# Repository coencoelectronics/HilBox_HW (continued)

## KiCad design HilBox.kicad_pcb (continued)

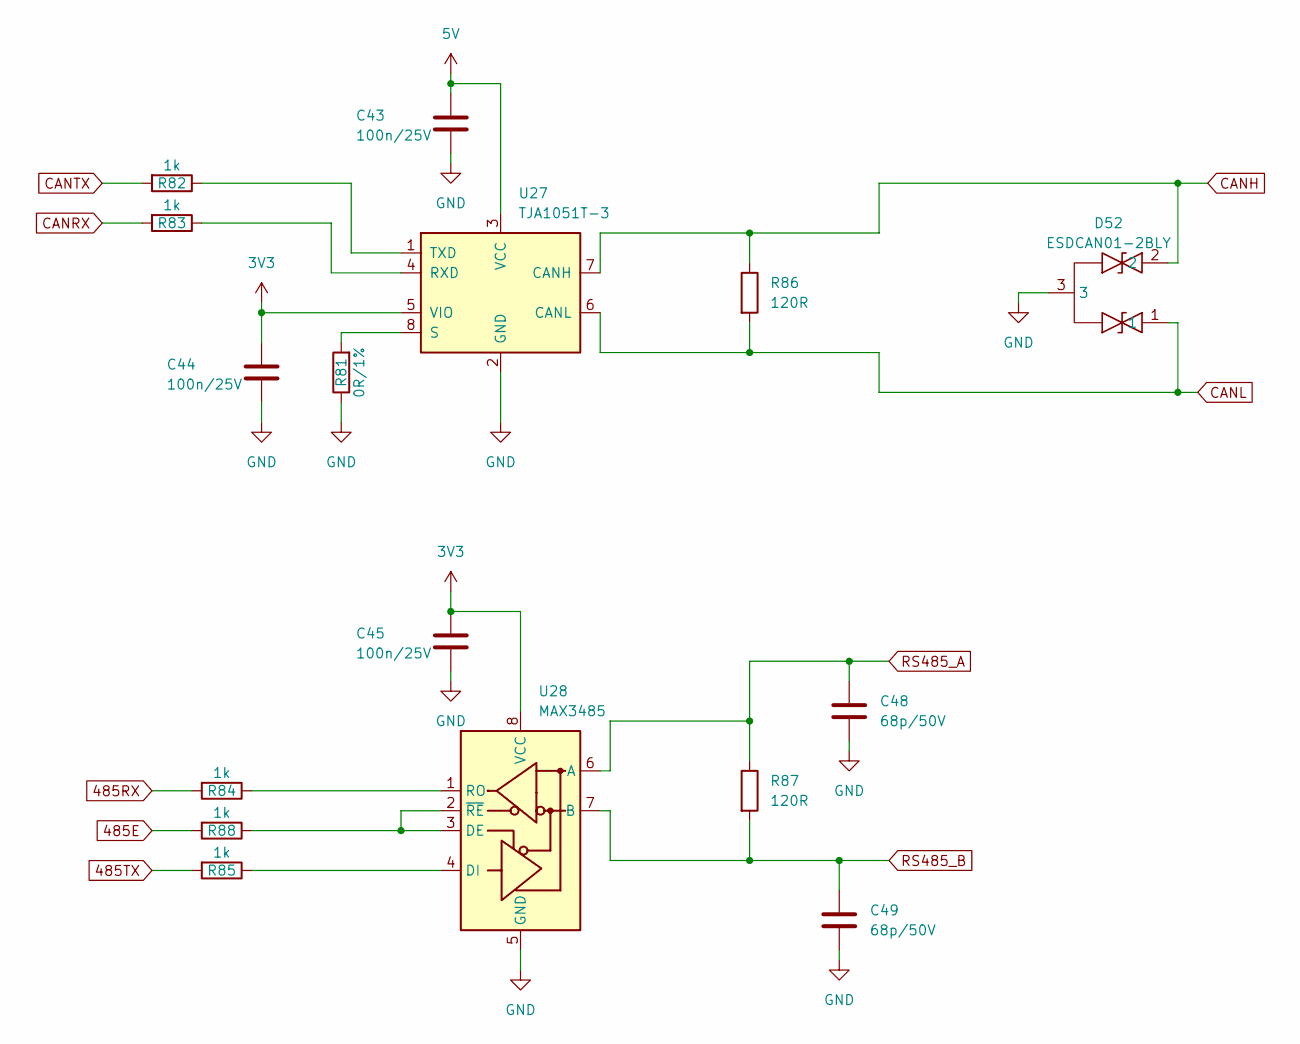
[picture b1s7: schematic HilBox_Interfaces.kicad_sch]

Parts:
C43, C44, C45: 100n/25V; C_0402_1005Metric; JLC_PN C77014
C48, C49: 68p/50V; C_0402_1005Metric; JLC_PN C77014
D52: ESDCAN01-2BLY; SOT-23-3
R81: 0R/1%; R_0603_1608Metric; JLC_PN C21189
R82, R83: 1k; R_1206_3216Metric; JLC_PN C1469
R84, R85, R88: 1k; R_0603_1608Metric; JLC_PN C23162
R86, R87: 120R; R_1210_3225Metric; JLC_PN C137105
U27: TJA1051T-3; SOIC-8_3.9x4.9mm_P1.27mm; JLC_PN C5342108
U28: MAX3485; SOIC-8_3.9x4.9mm_P1.27mm; JLC_PN C558792

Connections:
3V3: C44.1, C45.1, U27.5 (VIO), U28.8 (VCC); also elsewhere on the board
5V: C43.1, U27.3 (VCC); also elsewhere on the board
485E: R88.2; also elsewhere on the board
485RX: R84.2; also elsewhere on the board
485TX: R85.2; also elsewhere on the board
CANH: D52.2, R86.1, U27.7 (CANH); also elsewhere on the board
CANL: D52.1, R86.2, U27.6 (CANL); also elsewhere on the board
CANRX: R83.2; also elsewhere on the board
CANTX: R82.2; also elsewhere on the board
GND: C43.2, C44.2, C45.2, C48.2, C49.2, D52.3, R81.1, U27.2 (GND), U28.5 (GND); also elsewhere on the board
unnamed: R83.1, U27.4 (RXD)
unnamed: R81.2, U27.8 (S)
unnamed: R82.1, U27.1 (TXD)
unnamed: R88.1, U28.2 (~RE), U28.3 (DE)
unnamed: R85.1, U28.4 (DI)
unnamed: R84.1, U28.1 (RO)
RS485_A: C48.1, R87.1, U28.6 (A); also elsewhere on the board
RS485_B: C49.1, R87.2, U28.7 (B); also elsewhere on the board

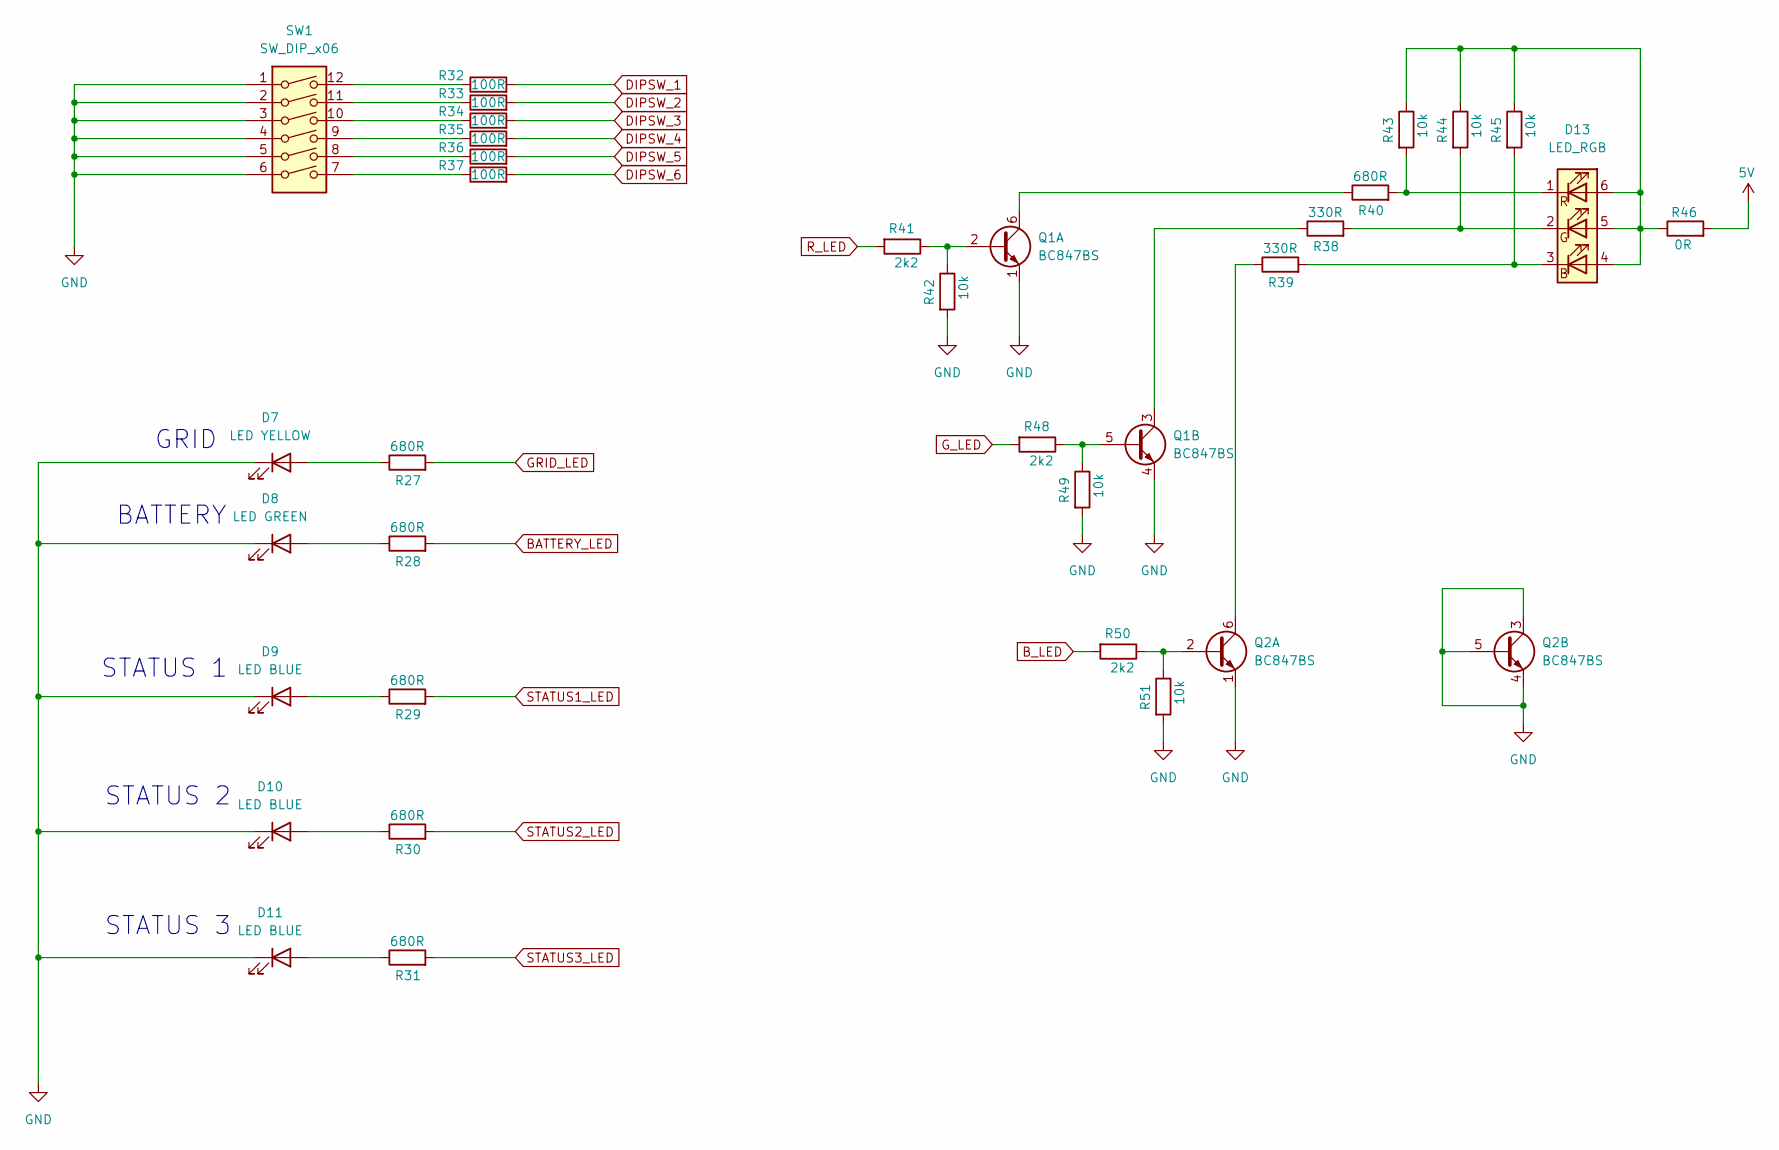
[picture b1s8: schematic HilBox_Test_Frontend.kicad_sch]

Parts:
D7: LED YELLOW; LED_0603_1608Metric; JLC_PN C2290
D8: LED GREEN; LED_0603_1608Metric; JLC_PN C84267
D9, D10, D11: LED BLUE; LED_0603_1608Metric; JLC_PN C2288
D13: LED_RGB; LED_RGB_5050-6; JLC_PN C784540
Q1, Q2: BC847BS; SOT-363_SC-70-6; JLC_PN C82368
R27, R28, R29, R30, R31: 680R; R_0603_1608Metric; JLC_PN C25177
R32, R33, R34, R35, R36, R37: 100R; R_0603_1608Metric; JLC_PN C25138
R38, R39: 330R; R_1206_3216Metric; JLC_PN C25374
R40: 680R; R_1206_3216Metric; JLC_PN C17975
R41, R48, R50: 2k2; R_0603_1608Metric; JLC_PN C4190
R42, R43, R44, R45, R49, R51: 10k; R_0603_1608Metric; JLC_PN C25804
R46: 0R; R_0603_1608Metric; JLC_PN C17168
SW1: SW_DIP_x06; SW_DIP_SPSTx06_Slide_6.7x16.8mm_W8.61mm_P2.54mm_LowProfile; JLC_PN C3293169

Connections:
5V: R46.2; also elsewhere on the board
BATTERY_LED: R28.2; also elsewhere on the board
B_LED: R50.2; also elsewhere on the board
DIPSW_1: R32.2; also elsewhere on the board
DIPSW_2: R33.2; also elsewhere on the board
DIPSW_3: R34.2; also elsewhere on the board
DIPSW_4: R35.2; also elsewhere on the board
DIPSW_5: R36.2; also elsewhere on the board
DIPSW_6: R37.2; also elsewhere on the board
GND: D7.1 (K), D8.1 (K), D9.1 (K), D10.1 (K), D11.1 (K), Q1.1 (E1), Q1.4 (E2), Q2.1 (E1), Q2.3 (C2), Q2.4 (E2), Q2.5 (B2), R42.2, R49.2, R51.2, SW1.1, SW1.2, SW1.3, SW1.4, SW1.5, SW1.6; also elsewhere on the board
GRID_LED: R27.2; also elsewhere on the board
G_LED: R48.2; also elsewhere on the board
unnamed: D7.2 (A), R27.1
unnamed: D8.2 (A), R28.1
unnamed: D9.2 (A), R29.1
unnamed: D10.2 (A), R30.1
unnamed: D11.2 (A), R31.1
unnamed: D13.4 (BA), D13.5 (GA), D13.6 (RA), R43.1, R44.1, R45.1, R46.1
unnamed: D13.3 (BK), R39.2, R45.2
unnamed: D13.2 (GK), R38.2, R44.2
unnamed: D13.1 (RK), R40.2, R43.2
unnamed: Q1.2 (B1), R41.1, R42.1
unnamed: Q1.6 (C1), R40.1
unnamed: Q1.5 (B2), R48.1, R49.1
unnamed: Q1.3 (C2), R38.1
unnamed: Q2.2 (B1), R50.1, R51.1
unnamed: Q2.6 (C1), R39.1
unnamed: R32.1, SW1.12
unnamed: R33.1, SW1.11
unnamed: R34.1, SW1.10
unnamed: R35.1, SW1.9
unnamed: R36.1, SW1.8
unnamed: R37.1, SW1.7
R_LED: R41.2; also elsewhere on the board
STATUS1_LED: R29.2; also elsewhere on the board
STATUS2_LED: R30.2; also elsewhere on the board
STATUS3_LED: R31.2; also elsewhere on the board

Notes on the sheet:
GRID
STATUS 2
STATUS 3
STATUS 1
BATTERY

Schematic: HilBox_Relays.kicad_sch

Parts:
D3, D12, D14, D15: RED; LED_0603_1608Metric; JLC_PN C72038
D4, D16, D19, D21: BAT46W; D_SOD-123; JLC_PN C83152
K1, K2, K3, K4: G6K-2F-Y-24V; RELAY_G6K-2F_DC5; JLC_PN C5278023
Q3, Q8, Q9, Q10: BC847BS; SOT-363_SC-70-6; JLC_PN C82368
R8, R165, R175, R178: 2k2; R_0603_1608Metric; JLC_PN C4190
R9, R11, R65, R67, R70, R164, R176, R177: 10k; R_0603_1608Metric; JLC_PN C25804
R10, R66, R68, R71: 100k; R_0603_1608Metric; JLC_PN C15458
R12, R64, R69, R72: 22k; R_0603_1608Metric; JLC_PN C23344

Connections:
GND: Q3.1 (E1), Q3.4 (E2), Q8.1 (E1), Q8.4 (E2), Q9.1 (E1), Q9.4 (E2), Q10.1 (E1), Q10.4 (E2), R10.2, R11.2, R66.2, R68.2, R71.2, R164.2, R176.2, R177.2; also elsewhere on the board
INAIL_IN: R67.2, R175.2; also elsewhere on the board
unnamed: D3.2 (A), R64.2
unnamed: D3.1 (K), Q9.3 (C2)
unnamed: D4.2 (A), K4.8, Q3.6 (C1)
unnamed: D12.2 (A), R69.2
unnamed: D12.1 (K), Q8.3 (C2)
unnamed: D14.2 (A), R72.2
unnamed: D14.1 (K), Q10.3 (C2)
unnamed: D15.2 (A), R12.2
unnamed: D15.1 (K), Q3.3 (C2)
unnamed: D16.2 (A), K1.8, Q9.6 (C1)
unnamed: D19.2 (A), K2.8, Q8.6 (C1)
unnamed: D21.2 (A), K3.8, Q10.6 (C1)
unnamed: Q3.2 (B1), R8.1, R11.1
unnamed: Q3.5 (B2), R9.1, R10.1
unnamed: Q8.2 (B1), R175.1, R176.1
unnamed: Q8.5 (B2), R67.1, R68.1
unnamed: Q9.2 (B1), R164.1, R165.1
unnamed: Q9.5 (B2), R65.1, R66.1
unnamed: Q10.2 (B1), R177.1, R178.1
unnamed: Q10.5 (B2), R70.1, R71.1
PMING_IN: R70.2, R178.2; also elsewhere on the board
RLY1_A: K1.3; also elsewhere on the board
RLY1_B: K1.4; also elsewhere on the board
RLY2_A: K2.3; also elsewhere on the board
RLY2_B: K2.4; also elsewhere on the board
RLY3_A: K3.3; also elsewhere on the board
RLY3_B: K3.4; also elsewhere on the board
RLY4_A: K4.3; also elsewhere on the board
RLY4_B: K4.4; also elsewhere on the board
RT_IN: R8.2, R9.2; also elsewhere on the board
TL_TF_IN: R65.2, R165.2; also elsewhere on the board
Vin: D4.1 (K), D16.1 (K), D19.1 (K), D21.1 (K), K1.1, K2.1, K3.1, K4.1, R12.1, R64.1, R69.1, R72.1; also elsewhere on the board

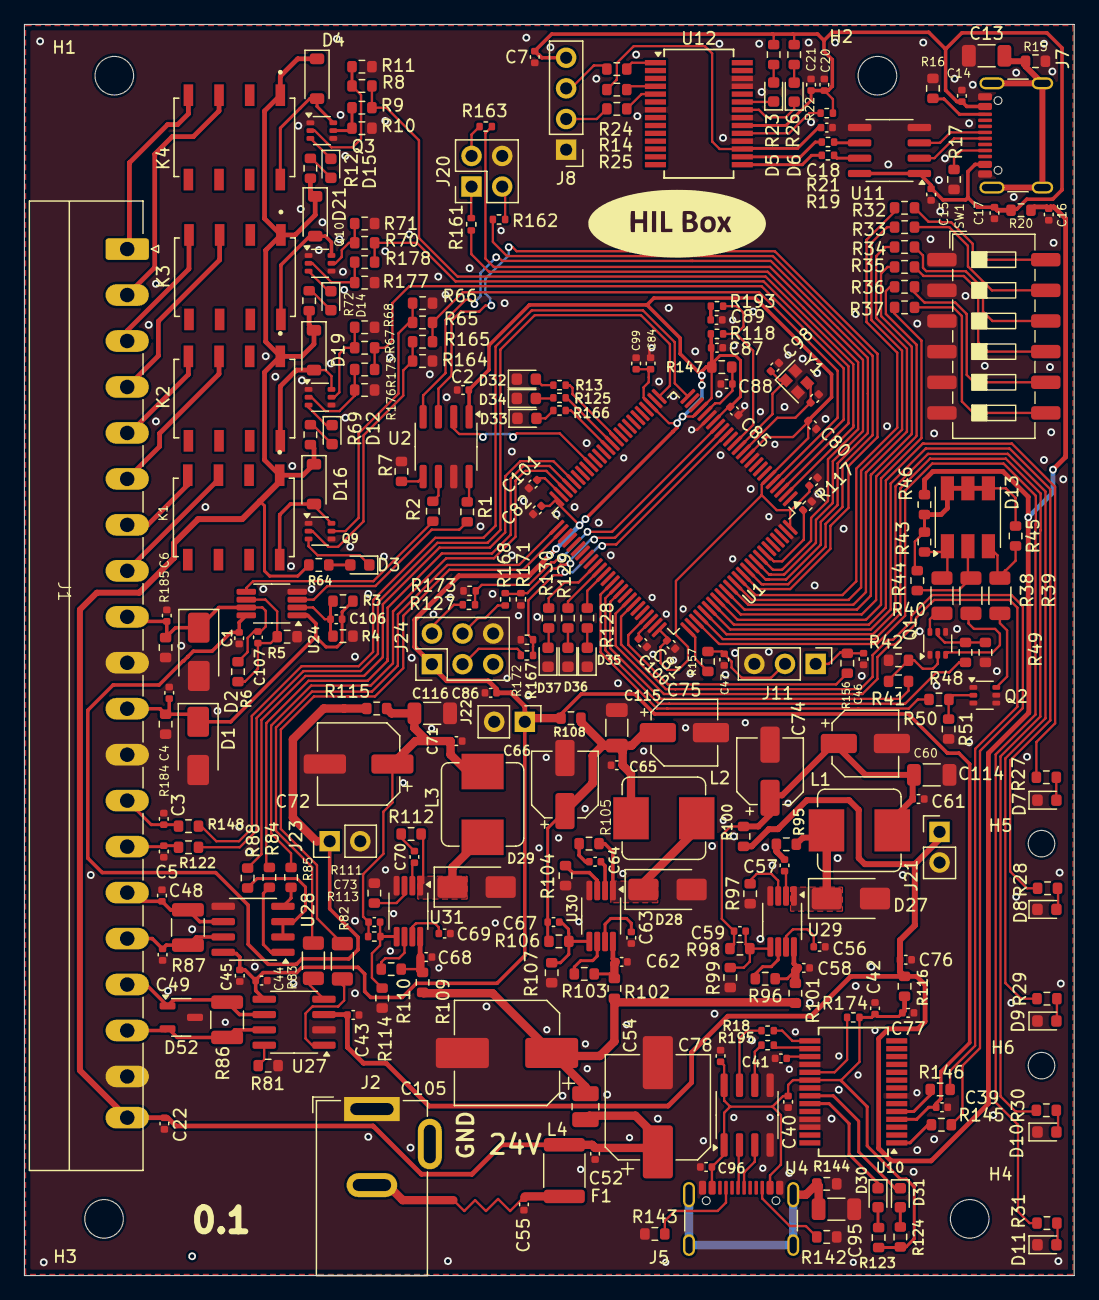
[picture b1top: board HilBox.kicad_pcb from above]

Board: 2 copper layers, 87.0 x 103.7 mm, 280 parts (0 on the bottom side), 209 nets.

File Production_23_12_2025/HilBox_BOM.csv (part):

"Reference","Value","Footprint","Qty","DNP","JLC_PN"
"C1","100n/25V","Capacitor_SMD:C_0402_1005Metric","1","","C77014"
"C2","100n/25V","Capacitor_SMD:C_0402_1005Metric","1","","C77014"
"C3","68p/50V","Capacitor_SMD:C_0402_1005Metric","1","","C77014"
"C4","68p/50V","Capacitor_SMD:C_0402_1005Metric","1","","C77014"
"C5","68p/50V","Capacitor_SMD:C_0402_1005Metric","1","","C77014"
"C6","68p/50V","Capacitor_SMD:C_0402_1005Metric","1","","C77014"
"C7","100n/25V","Capacitor_SMD:C_0402_1005Metric","1","","C77014"
"C13","1n/2kV","Capacitor_SMD:C_1206_3216Metric","1","","C23631"
"C14","100n/25V","Capacitor_SMD:C_0402_1005Metric","1","","C77014"
"C15","100n/25V","Capacitor_SMD:C_0402_1005Metric","1","","C77014"
"C16","100n/25V","Capacitor_SMD:C_0402_1005Metric","1","","C77014"
"C17","100n/25V","Capacitor_SMD:C_0402_1005Metric","1","","C77014"
"C18","100n/25V","Capacitor_SMD:C_0402_1005Metric","1","","C77014"
"C20","100n/25V","Capacitor_SMD:C_0402_1005Metric","1","","C77014"
"C21","4u7/10V","Capacitor_SMD:C_0402_1005Metric","1","","C23733 "
"C22","100n/50V","Capacitor_SMD:C_0402_1005Metric","1","","C77014"
"C39","100n/25V","Capacitor_SMD:C_0402_1005Metric","1","","C77014"
"C40","100n/25V","Capacitor_SMD:C_0402_1005Metric","1","","C77014"
"C41","100n/25V","Capacitor_SMD:C_0402_1005Metric","1","","C77014"
"C42","4u7/10V","Capacitor_SMD:C_0402_1005Metric","1","","C23733 "
"C43","100n/25V","Capacitor_SMD:C_0402_1005Metric","1","","C77014"
"C44","100n/25V","Capacitor_SMD:C_0402_1005Metric","1","","C77014"
"C45","100n/25V","Capacitor_SMD:C_0402_1005Metric","1","","C77014"
"C46","100pF","Capacitor_SMD:C_0402_1005Metric","1","","C1546 "
"C47","100pF","Capacitor_SMD:C_0402_1005Metric","1","","C1546 "
"C48","68p/50V","Capacitor_SMD:C_0402_1005Metric","1","","C77014"
"C49","68p/50V","Capacitor_SMD:C_0402_1005Metric","1","","C77014"
"C52","100n/50V","Capacitor_SMD:C_0402_1005Metric","1","","C77014"
"C54","220u 35V","Capacitor_SMD:CP_Elec_8x10.5","1",""," C3340"
"C55","68p/50V","Capacitor_SMD:C_0402_1005Metric","1","","C77014"
"C56","100n/25V","Capacitor_SMD:C_0402_1005Metric","1","","C77014"
"C57","100n/25V","Capacitor_SMD:C_0402_1005Metric","1","","C77014"
"C58","100n/50V","Capacitor_SMD:C_0402_1005Metric","1","","C77014"
"C60","100u 10V","Capacitor_SMD:CP_Elec_5x5.3","1",""," C3347"
"C61","100n/25V","Capacitor_SMD:C_0402_1005Metric","1","","C77014"
"C62","100n/50V","Capacitor_SMD:C_0402_1005Metric","1","","C77014"
"C63","100n/25V","Capacitor_SMD:C_0402_1005Metric","1","","C77014"
"C64","100n/25V","Capacitor_SMD:C_0402_1005Metric","1","","C77014"
"C65","100n/25V","Capacitor_SMD:C_0402_1005Metric","1","","C77014"
"C66","100u 10V","Capacitor_SMD:CP_Elec_5x5.3","1",""," C3347"
"C68","100n/50V","Capacitor_SMD:C_0402_1005Metric","1","","C77014"
"C69","100n/25V","Capacitor_SMD:C_0402_1005Metric","1","","C77014"
"C70","100n/25V","Capacitor_SMD:C_0402_1005Metric","1","","C77014"
"C71","100n/25V","Capacitor_SMD:C_0402_1005Metric","1","","C77014"
"C72","47u 25V","Capacitor_SMD:CP_Elec_6.3x5.4","1","","C30034"
"C76","100n/25V","Capacitor_SMD:C_0402_1005Metric","1","","C77014"
"C77","100n/25V","Capacitor_SMD:C_0402_1005Metric","1","","C77014"
"C78","100n/25V","Capacitor_SMD:C_0402_1005Metric","1","","C77014"
"C80","100n/25V","Capacitor_SMD:C_0402_1005Metric","1","","C77014"
"C81","100n/25V","Capacitor_SMD:C_0402_1005Metric","1","","C77014"
"C82","100n/25V","Capacitor_SMD:C_0402_1005Metric","1","","C77014"
"C83","100n/25V","Capacitor_SMD:C_0402_1005Metric","1","","C77014"
"C84","100n/25V","Capacitor_SMD:C_0402_1005Metric","1","","C77014"
"C85","100n/25V","Capacitor_SMD:C_0402_1005Metric","1","","C77014"
"C86","100n/25V","Capacitor_SMD:C_0402_1005Metric","1","","C77014"
"C87","100n/25V","Capacitor_SMD:C_0402_1005Metric","1","","C77014"
"C88","100n/25V","Capacitor_SMD:C_0402_1005Metric","1","","C77014"
"C89","100n/25V","Capacitor_SMD:C_0402_1005Metric","1","","C77014"
"C95","1n/2kV","Capacitor_SMD:C_1206_3216Metric","1","","C23631"
"C96","100n/25V","Capacitor_SMD:C_0402_1005Metric","1","","C77014"
"C97","10p","Capacitor_SMD:C_0402_1005Metric","1","","C1545 "
"C98","10p","Capacitor_SMD:C_0402_1005Metric","1","","C1545 "
"C99","4u7/10V","Capacitor_SMD:C_0402_1005Metric","1","","C23733 "
"C100","2u2/10V","Capacitor_SMD:C_0402_1005Metric","1","","C60078"
"C101","2u2/10V","Capacitor_SMD:C_0402_1005Metric","1","","C60078"
"C105","220u 35V","Capacitor_SMD:CP_Elec_8x10.5","1",""," C3340"
"C114","10u/25V","Capacitor_SMD:C_1206_3216Metric","1","","C9807"
"C115","10u/25V","Capacitor_SMD:C_1206_3216Metric","1","","C9807"
"C116","10u/25V","Capacitor_SMD:C_1206_3216Metric","1","","C9807"
"D1","SMAJ12A","Diode_SMD:D_SMA","1","","C113957"
"D2","SMAJ12A","Diode_SMD:D_SMA","1","","C113957"
"D3","RED","LED_SMD:LED_0603_1608Metric","1","","  C72038"
"D4","BAT46W","Diode_SMD:D_SOD-123","1","","C83152"
"D5","BLUE","LED_SMD:LED_0603_1608Metric","1","","C2288"
"D6","WHITE","LED_SMD:LED_0603_1608Metric","1",""," C2290"
"D7","LED YELLOW","LED_SMD:LED_0603_1608Metric","1","","C2290"
"D8","LED GREEN","LED_SMD:LED_0603_1608Metric","1","","C84267"
"D9","LED BLUE","LED_SMD:LED_0603_1608Metric","1","","C2288"
"D10","LED BLUE","LED_SMD:LED_0603_1608Metric","1","","C2288"
"D11","LED BLUE","LED_SMD:LED_0603_1608Metric","1","","C2288"
"D12","RED","LED_SMD:LED_0603_1608Metric","1","","  C72038"
"D13","LED_RGB","LED_SMD:LED_RGB_5050-6","1","","C784540"
"D14","RED","LED_SMD:LED_0603_1608Metric","1","","  C72038"
"D15","RED","LED_SMD:LED_0603_1608Metric","1","","  C72038"
"D16","BAT46W","Diode_SMD:D_SOD-123","1","","C83152"
"D19","BAT46W","Diode_SMD:D_SOD-123","1","","C83152"
"D21","BAT46W","Diode_SMD:D_SOD-123","1","","C83152"
"D27","SS14","Diode_SMD:D_SMA","1","","C2480"
"D28","SS14","Diode_SMD:D_SMA","1","","C2480"
"D29","SS14","Diode_SMD:D_SMA","1","","C2480"
"D30","BLUE","LED_SMD:LED_0603_1608Metric","1","","C2288"
"D31","WHITE","LED_SMD:LED_0603_1608Metric","1",""," C2290"
"D32","RED","LED_SMD:LED_0603_1608Metric","1","","  C72038"
"D33","RED","LED_SMD:LED_0603_1608Metric","1","","  C2286"
"D34","RED","LED_SMD:LED_0603_1608Metric","1","","  C2286"
"D35","RED_","LED_SMD:LED_0603_1608Metric","1","","C2286"
"D36","RED_","LED_SMD:LED_0603_1608Metric","1","","C2286"
"D37","RED_","LED_SMD:LED_0603_1608Metric","1","","C2286"
"D52","ESDCAN01-2BLY","Package_TO_SOT_SMD:SOT-23-3","1","",""
"F1","PTC 30V 500mA","Resistor_SMD:R_1812_4532Metric","1","","C12559"
"J1","Conn_01x20_Pin","Connectors:Terminal_Block_3_81_20p_Horizontal","1","","C430380"
"J2","Jack-DC","Connector_BarrelJack:BarrelJack_GCT_DCJ200-10-A_Horizontal","1","",""
"J5","USB_C_Plug_USB2.0","Connector_USB:USB_C_Receptacle_GCT_USB4105-xx-A_16P_TopMnt_Horizontal","1","","C393939"
"J7","USB_C_Plug_USB2.0","Connector_USB:USB_C_Receptacle_GCT_USB4105-xx-A_16P_TopMnt_Horizontal","1","","C393939"
"J8","Conn_01x04_Pin","Connector_PinHeader_2.54mm:PinHeader_1x04_P2.54mm_Vertical","1","",""
"J11","Conn_01x03_Pin","Connector_PinHeader_2.54mm:PinHeader_1x03_P2.54mm_Vertical","1","","C49257 "
"J21","Conn_01x02_Pin","Connector_PinHeader_2.54mm:PinHeader_1x02_P2.54mm_Vertical","1","","C225477"
"J22","Conn_01x02_Pin","Connector_PinHeader_2.54mm:PinHeader_1x02_P2.54mm_Vertical","1","","C225477"
"J23","Conn_01x02_Pin","Connector_PinHeader_2.54mm:PinHeader_1x02_P2.54mm_Vertical","1","","C225477"
"K1","G6K-2F-Y-24V","Relays:RELAY_G6K-2F_DC5","1","","C5278023"
"K2","G6K-2F-Y-24V","Relays:RELAY_G6K-2F_DC5","1","","C5278023"
"K3","G6K-2F-Y-24V","Relays:RELAY_G6K-2F_DC5","1","","C5278023"
"K4","G6K-2F-Y-24V","Relays:RELAY_G6K-2F_DC5","1","","C5278023"
"L1","47uH 2A","Inductor_SMD:L_Bourns_SRP7028A_7.3x6.6mm","1","","C5189962"
"L2","47uH 2A","Inductor_SMD:L_Bourns_SRP7028A_7.3x6.6mm","1","","C5189962"
"L3","47uH 2A","Inductor_SMD:L_Bourns_SRP7028A_7.3x6.6mm","1","","C5189962"
"L4","1uH/1.6A","Inductor_SMD:L_1008_2520Metric","1","","C86091"
"Q1","BC847BS","Package_TO_SOT_SMD:SOT-363_SC-70-6","1","","C82368"
"Q2","BC847BS","Package_TO_SOT_SMD:SOT-363_SC-70-6","1","","C82368"
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
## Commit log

2025-12-19 Modification in half of target
2025-12-19 Schematic design at finish
2025-12-21 Backup
2025-12-22 Layout 90% done
2025-12-23 Gate finalized! PCB ordered
